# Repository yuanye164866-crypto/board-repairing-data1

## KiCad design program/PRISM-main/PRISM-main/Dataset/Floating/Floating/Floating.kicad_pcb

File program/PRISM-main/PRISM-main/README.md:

# PRISM

**PCB Recognition and Intelligent Schematic Mapping**

PRISM reconstructs an editable KiCad schematic from aligned images of the top
and bottom sides of a PCB. It combines image processing, pad and trace
detection, OCR-assisted component recognition, connectivity analysis, manual
correction tools, and schematic optimization in one desktop application.

> PRISM is currently alpha software. Generated connectivity and component
> assignments must be reviewed before they are used for manufacturing,
> servicing, or safety-critical work.

## Features

- guided import of TOP and BOTTOM PCB images;
- automatic or manually sampled solder-mask and copper colors;
- board alignment, pad pairing, trace detection, and net reconstruction;
- OCR-assisted labels and component candidates;
- interactive correction editor for pads, traces, pairs, OCR, and components;
- text netlist and KiCad schematic export;
- optional KiCad CLI validation and schematic optimization;
- native desktop builds for Windows, macOS, and Linux.

## Requirements

- Python 3.11 or newer when running from source;
- Tk 8.6 or newer;
- Tesseract OCR for OCR features;
- KiCad with `kicad-cli` for round-trip validation and optimized previews.

PRISM searches `PATH` first and then conventional installation locations for
the current operating system. Tesseract can also be selected manually in the
interface.

On Debian or Ubuntu, install the native GUI and OpenCV runtime libraries before
running from source or building:

```bash
sudo apt-get install python3-venv python3-tk libgl1 libglib2.0-0
```

## Run From Source

Create and activate a virtual environment, then install the project:

```bash
python -m venv .venv
```

Windows PowerShell:

```powershell
.\.venv\Scripts\Activate.ps1
python -m pip install -r requirements.txt
prism
```

macOS and Linux:

```bash
source .venv/bin/activate
python -m pip install -r requirements.txt
prism
```

Windows users can alternatively run `.\run.ps1`.

## Build Native Packages

PyInstaller creates native applications and does not cross-compile. Run the
matching script on each target operating system:

```powershell
# Windows
.\scripts\build\build_windows.ps1
```

```bash
# macOS
bash scripts/build/build_macos.sh

# Linux
bash scripts/build/build_linux.sh
```

The scripts create an isolated `.venv-build` environment and use the shared
configuration in `scripts/build/package.py`.

| Platform | Output |
| --- | --- |
| Windows | `dist/PRISM/PRISM.exe` |
| macOS | `dist/PRISM.app` |
| Linux | `dist/PRISM/PRISM` |

Windows and Linux use PyInstaller's `onedir` layout. Distribute the complete
`dist/PRISM` directory, not only the executable. The macOS application is
unsigned; public releases should be code-signed and notarized by the release
owner.

## Basic Workflow

1. Select images of the top and bottom PCB sides.
2. Confirm automatic color detection or collect color samples manually.
3. Run the analysis.
4. Review detected geometry and connectivity in the correction editor.
5. Recalculate after corrections and inspect the generated netlist.
6. Open the result directory and validate the KiCad schematic.

Generated files are written under `~/PRISM/results` by default. Set the
`PRISM_OUTPUT_DIR` environment variable to use a different location. A local
`results/` directory is also excluded from version control.

## Dataset

[`Dataset/`](Dataset/README.md) contains twelve PCB examples with TOP/BOTTOM
images and reference KiCad projects. It is intended for repeatable development
and evaluation, not as a formal train/test split.

## Reproducible Evaluation

[`evaluation/`](evaluation/README.md) contains the versioned reference
annotations and English-language tools for synthetic regression tests and
ablation studies. A baseline run is started from the repository root with:

```bash
python evaluation/run_evaluation.py
```

The six supported ablation configurations can be executed with:

```bash
python evaluation/run_ablations.py
```

The tools generate machine-readable JSON reports, compact Markdown summaries,
and a LaTeX ablation table under `evaluation/results/`. See the
[evaluation guide](evaluation/README.md) for sample selection, dependency
requirements, command-line options, report interpretation, and the exact scope
of the synthetic results. These tests exercise controlled KiCad-derived board
images; they do not validate PRISM on photographs of physical PCBs.

## Project Structure

```text
.
|-- Dataset/                         Test images and reference KiCad projects
|-- evaluation/                      Synthetic evaluation, ablations, and reference annotations
|-- scripts/build/                   Native build entry points and shared build logic
|-- src/schematic_generator/
|   |-- assets/                      Application and executable icons
|   |-- correction_editor/           Manual reconstruction editor
|   |-- detection/                   Pad, trace, plane, and pair detection
|   |-- diagnostics/                 Diagnostic reports
|   |-- geometry/                    Alignment and rectification
|   |-- gui/                         Main desktop workflow
|   |-- kicad/                       KiCad serialization and routing
|   |-- netlist/                     Connectivity and component inference
|   |-- schematic/                   Validation and optimization
|   |-- platform_support.py          Operating-system integration
|   `-- __main__.py                  Application entry point
|-- pyproject.toml                  Package metadata and runtime dependencies
|-- requirements-build.txt          Build-only dependencies
`-- requirements.txt                Editable development installation
```

## Automated Builds

The GitHub Actions workflow in `.github/workflows/build.yml` runs smoke tests
and creates Windows, macOS, and Linux artifacts using the same scripts as local
builds.

## Contributing

Keep platform-independent behavior in the application modules. Operating-system
differences belong in `platform_support.py`, while packaging differences belong
in `scripts/build/package.py`. New detection or reconstruction behavior should
be checked against multiple samples from `Dataset/`.

## License

No project license has been selected yet. Add a `LICENSE` file before presenting
PRISM as open-source software or accepting external contributions.

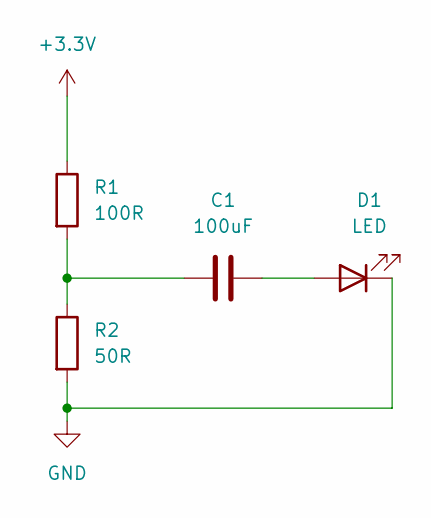
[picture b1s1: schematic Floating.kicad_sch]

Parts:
C1: 100uF; CP_Radial_Tantal_D8.0mm_P2.50mm
D1: LED; LED_D10.0mm
R1: 100R; R_Axial_DIN0309_L9.0mm_D3.2mm_P12.70mm_Horizontal
R2: 50R; R_Axial_DIN0411_L9.9mm_D3.6mm_P5.08mm_Vertical

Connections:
+3.3V: R1.1
GND: D1.1 (K), R2.2
unnamed: C1.1, R1.2, R2.1
unnamed: C1.2, D1.2 (A)

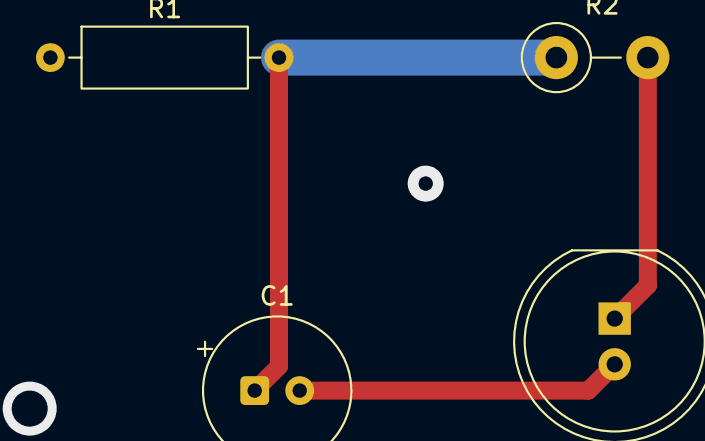
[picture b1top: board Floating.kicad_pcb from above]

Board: 2 copper layers, 4 parts (0 on the bottom side), 3 nets.
